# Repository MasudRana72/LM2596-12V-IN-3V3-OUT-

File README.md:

# LM2596-12V-IN-3V3-OUT-
This is a buck regulator. Convert 12V DC to 3V3 DC.

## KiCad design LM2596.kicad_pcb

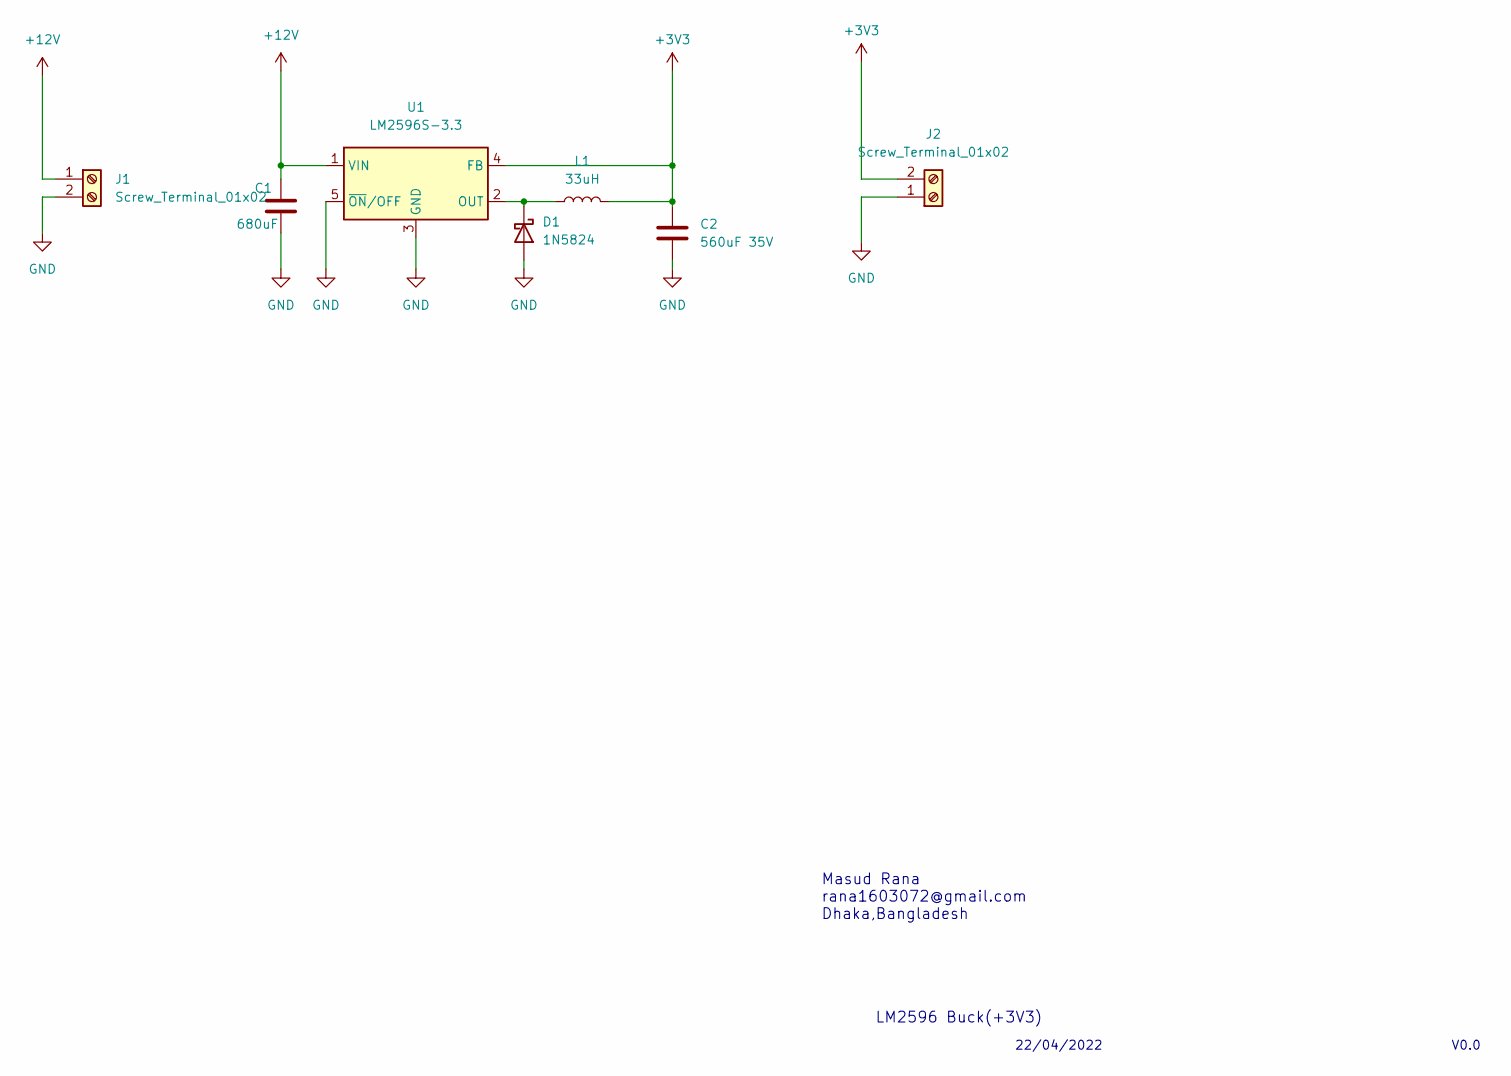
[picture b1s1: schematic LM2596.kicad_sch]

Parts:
C1: 680uF; C_Elec_10x10.2
C2: 560uF 35V; C_Elec_10x10.2
D1: 1N5824; DO-214AB
J1, J2: Screw_Terminal_01x02; TerminalBlock_Phoenix_MKDS-1,5-2-5.08_1x02_P5.08mm_Horizont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
L1: 33uH; L_Bourns_SRR1260
U1: LM2596S-3.3; TO-252-5_TabPin3

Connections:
+3V3: C2.1, J2.2, L1.2, U1.4 (FB)
+12V: C1.1, J1.1, U1.1 (VIN)
GND: C1.2, C2.2, D1.2 (A), J1.2, J2.1, U1.3 (GND), U1.5 (~ON/OFF)
unnamed: D1.1 (K), L1.1, U1.2 (OUT)

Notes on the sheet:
V0.0
22/04/2022
Masud Rana rana1603072@gmail.com Dhaka,Bangladesh
LM2596 Buck(+3V3)

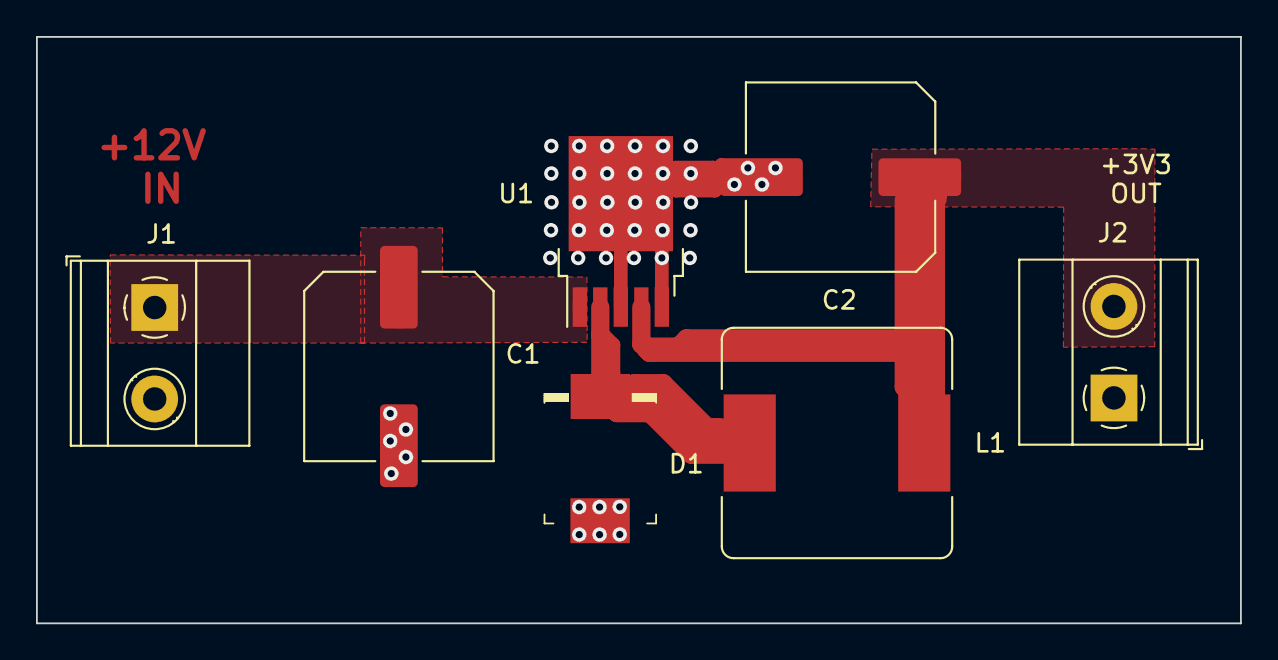
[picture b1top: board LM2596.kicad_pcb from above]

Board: 2 copper layers, 66.9 x 32.6 mm, 7 parts (0 on the bottom side), 4 nets.

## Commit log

2022-04-22 Create Kicad Schematic File
